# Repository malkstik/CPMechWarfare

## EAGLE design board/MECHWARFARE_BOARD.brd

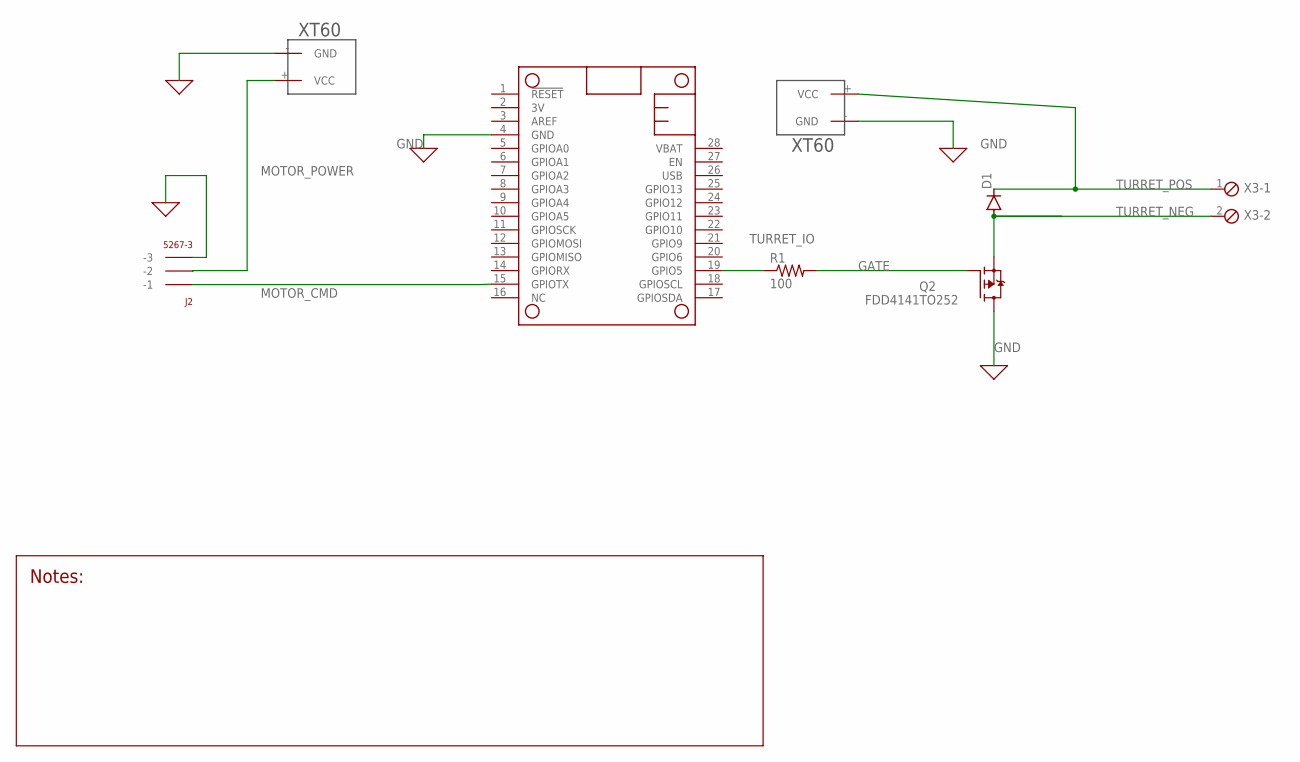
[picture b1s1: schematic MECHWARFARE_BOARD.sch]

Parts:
D1: DIODE-DO-214AC; DO-214AC
J2: 5267-3
MS2: FEATHERWINGEXTENDED_BOTH_ENDS; FEATHERWING
Q2: FDD4141TO252; TO252
R1: 100; R0805
U$1, U$2: XT60
X3: SCREWTERM_2P_254; 2POL254

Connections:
GATE: Q2.1 (G), R1.2
GND: J2.P$3 (-3), MS2.4 (GND), Q2.3 (D), U$1.- (GND), U$2.- (GND)
MOTOR_CMD: J2.P$1 (-1), MS2.15 (GPIOTX)
MOTOR_POWER: J2.P$2 (-2), U$1.+ (VCC)
TURRET_IO: MS2.19 (GPIO5), R1.1
TURRET_NEG: D1.A, Q2.2 (S), X3.2
TURRET_POS: D1.C, U$2.+ (VCC), X3.1

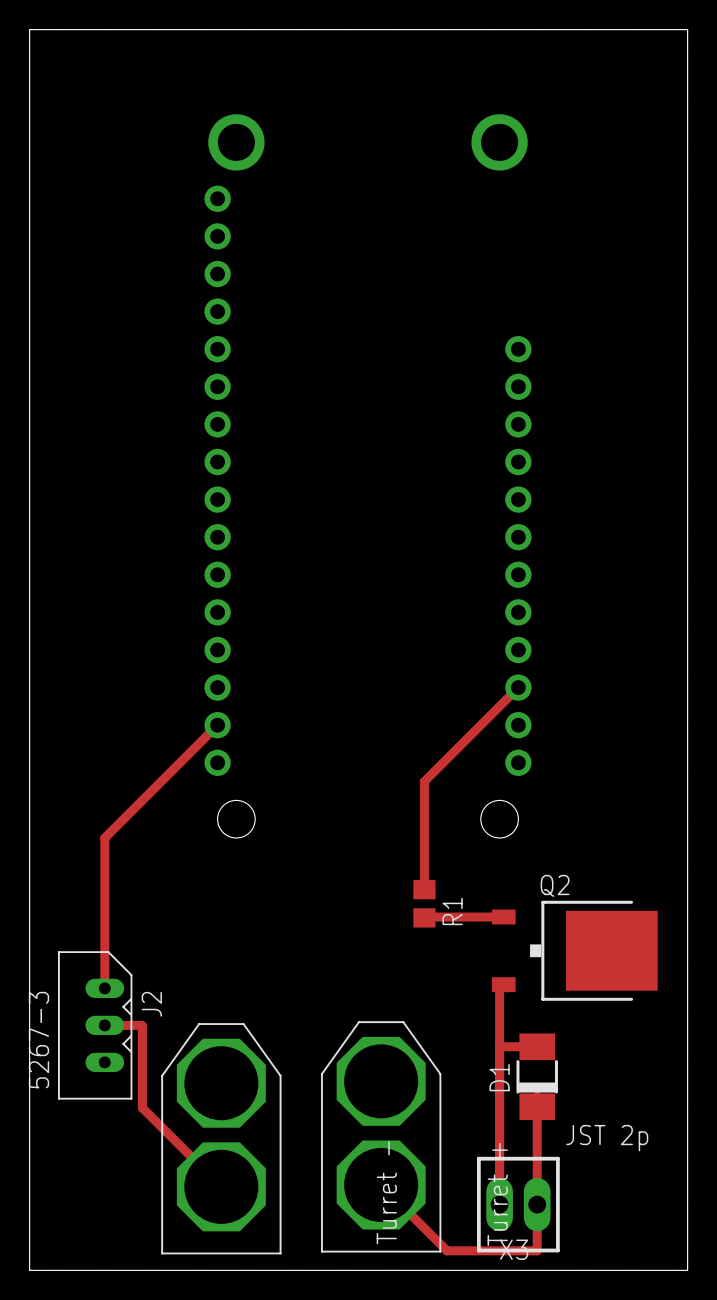
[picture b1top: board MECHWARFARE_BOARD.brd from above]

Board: 2 copper layers, 44.5 x 83.8 mm, 8 parts (0 on the bottom side), 7 nets.

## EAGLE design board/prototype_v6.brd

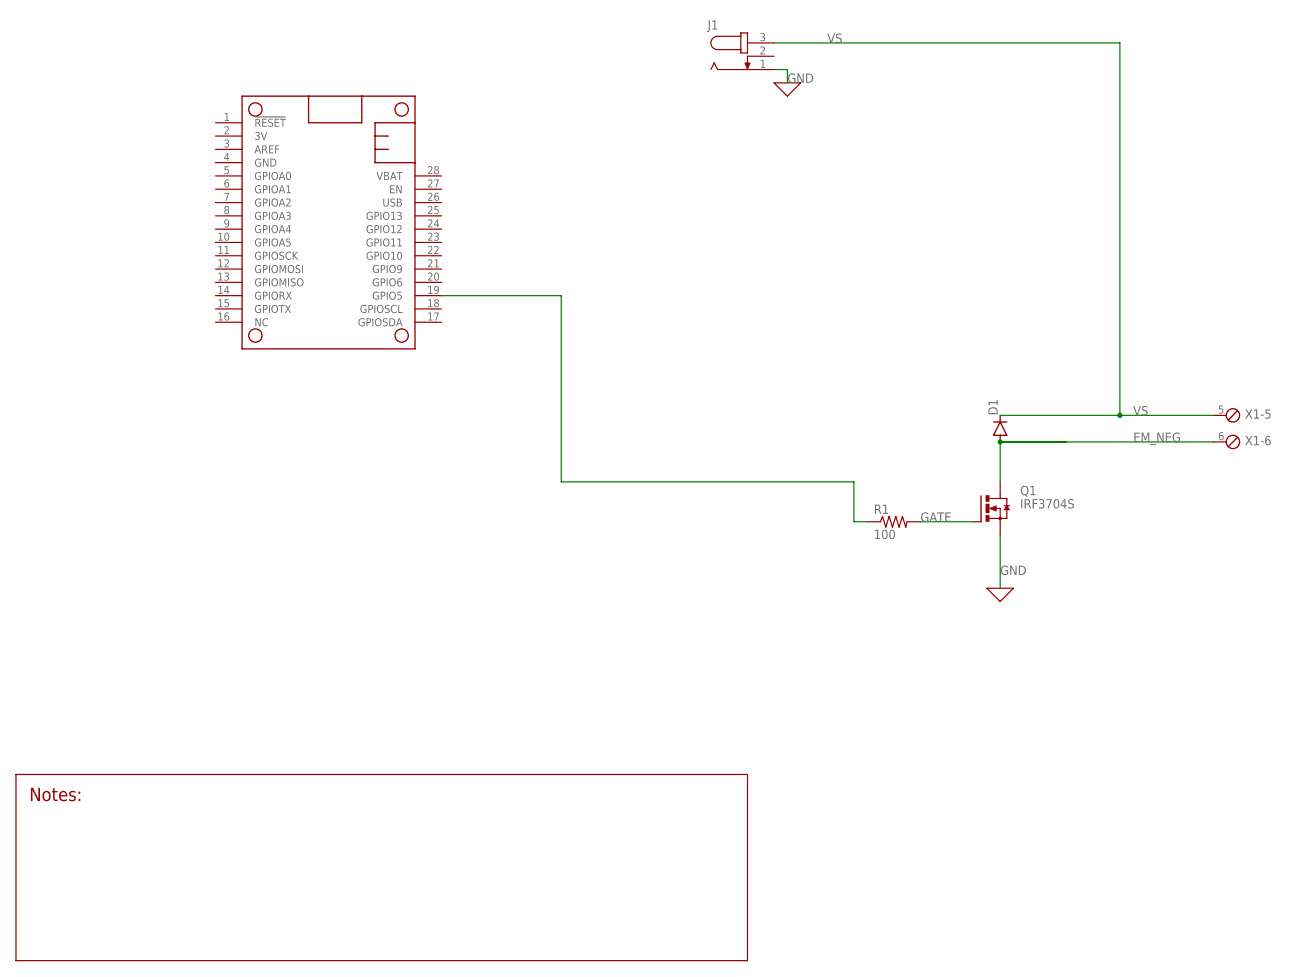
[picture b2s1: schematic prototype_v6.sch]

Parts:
D1: DIODE-DO-214AC; DO-214AC
J1: JACK-PLUG1; SPC4078
MS1: FEATHERWINGEXTENDED_BOTH_ENDS; FEATHERWING
Q1: IRF3704S; D2PACK
R1: 100; R0805
X1: SCREWTERM_6P_381; 6POL381

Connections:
EM_NEG: D1.A, Q1.2 (D), X1.6
GATE: Q1.1 (G), R1.2
GND: J1.1, MS1.4 (GND), Q1.3 (S)
unnamed: MS1.19 (GPIO5), R1.1
VS: D1.C, J1.3, X1.5

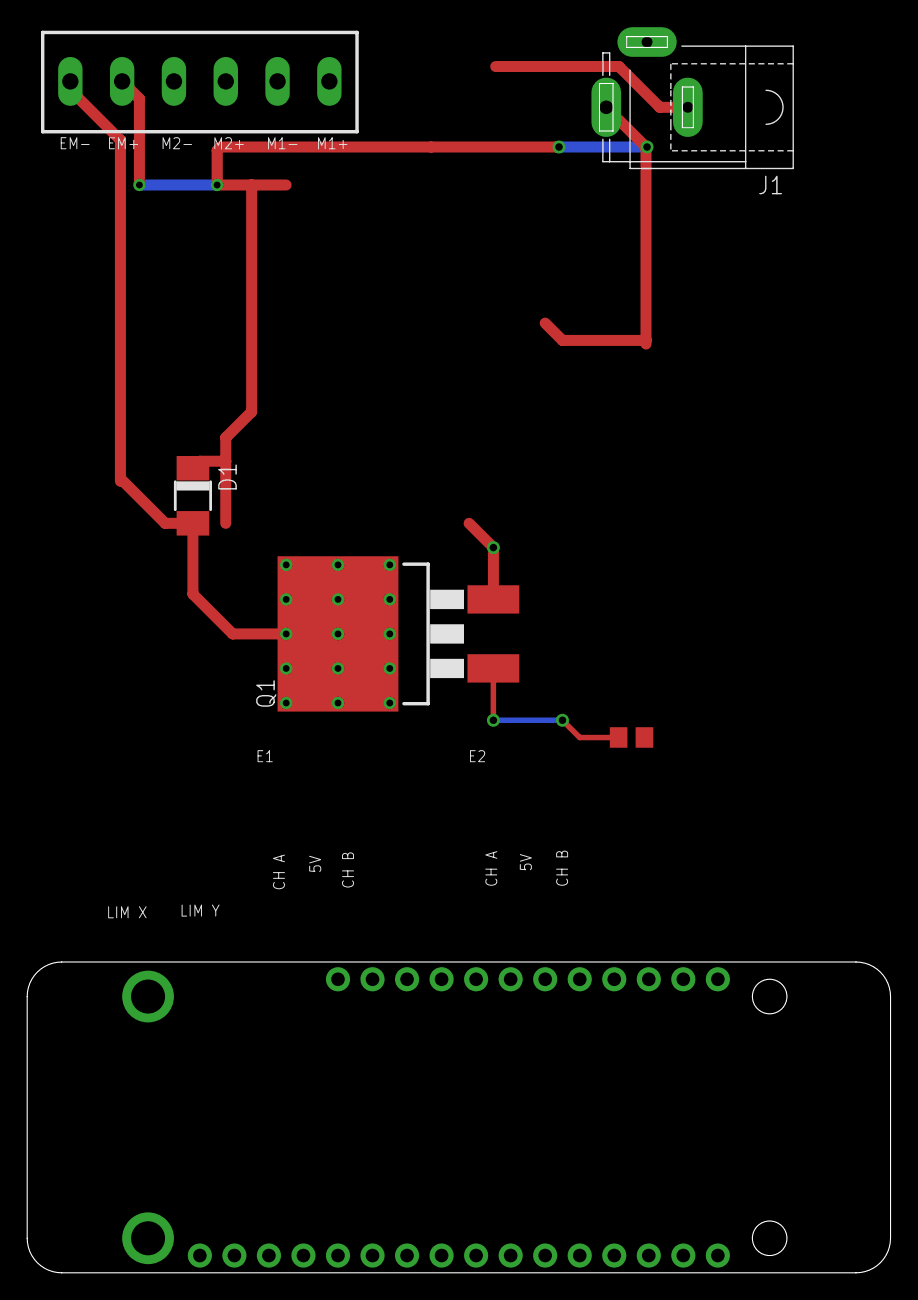
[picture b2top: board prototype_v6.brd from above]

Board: 2 copper layers, 63.5 x 90.9 mm, 6 parts (0 on the bottom side), 5 nets.

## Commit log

2022-01-22 first commit!
2022-02-12 stuff
2022-02-12 some framework
2022-02-12 dynamixel lib added
2022-02-17 NimBLE
    Added NimBLE and ESP32-BLE-Gamepad libraries to project
2022-04-26 uploading board and schematic
    custom pcb for using motor and turret
2022-04-26 giving access to necessary libs
2022-04-26 deleted extraneous files
2022-04-26 Minor Changes
    Added JST for airsoft power and adjusted some component locations.
2022-04-26 renamed a trace
2022-04-27 Connector Change
    Switched back to xt60 and removed duplicate files.
2022-04-30 Moved GND plane to bottom
    Moved the ground plane on the board from top to bottom and added heat sink for transistor.
